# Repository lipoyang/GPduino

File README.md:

GPduino
=========

## 概要
GPduinoは、Arduino+Konashi互換のBLEラジコン制御ボードです。  
GPduinoに関する詳細は、[GPduino特設ページ](http://lipoyang.net/gpduino)をごらんください。  
GPduinoの回路/基板設計データとプリセットファームウェアのソースをここに公開します。

## ファイル一覧

* firm/GPduinoR3/ : ファームウェア(Arduino Pro Mini 3.3V 互換のスケッチ)
* hard/GPduinoPCB/
	* GPduino.sch/brd: 回路/基板設計データ(Eagle形式)
	* GPduino.pdf: 回路図(PDF)
	* GPduino_BOM.xlsx: BOMリスト(Excel形式)
	* GPduino.GBL/GBO/GBP/GBS/GML/GTL/GTO/GTP/GTS/TXT: ガーバデータ
* LICENSE: Apache Licence 2.0です。
	* ただし、回路/基板設計は、Creative Commons Attribution Share-Alike 3.0です。
* README.md これ

## ブートローダの書き込み
部品実装したGPduino基板をArduinoとして使用できるようにするには、まずブートローダを書き込みます。
* ISPコネクタ（CN12）にISPプログラマーを接続します。向きに注意してください。
	* 3.3V系のArduino (Arduino Pro Mini 3.3V版など)をISPプログラマーにすることができます。
	* File > Examples > Arduino ISP をArduinoに書き込んでください。
* Arduino IDEにて、Tools > Board で、Arduino Pro or Pro Mini を選びます。
* Tools > Processor で、ATmega328(3.3V, 8MHz) を選びます。
* Tools > Programmer で、ISPプログラマーを選びます。
	* 上記の、Arduinoを使ったISPプログラマーの場合は、Arduino as ISPを選んでください。
* Tools > Burn Bootloader で、ブートローダーを書き込みます。

## ファームウェアの書き込み
GPduinoは、Arduino Pro Mini 3.3V版互換機です。
* 書き込みはArduino Pro Miniと同様、USBシリアル変換基板が必要です。CN13に接続してください。
	* SparkFun製 FTDI Basic Breakout - 3.3V を推奨します。かならず、3.3Vのものを使用してください。
* 基板のジャンパJ3を[USB]側に設定してください。
* Arduino IDEにて、Tools > Board で、Arduino Pro or Pro Mini を選びます。
* Tools > Processor で、ATmega328(3.3V, 8MHz) を選びます。
* Tools > Port で、USBシリアルのポート番号を選びます。
* Uploadボタンで、ファームウェアを書き込みます。

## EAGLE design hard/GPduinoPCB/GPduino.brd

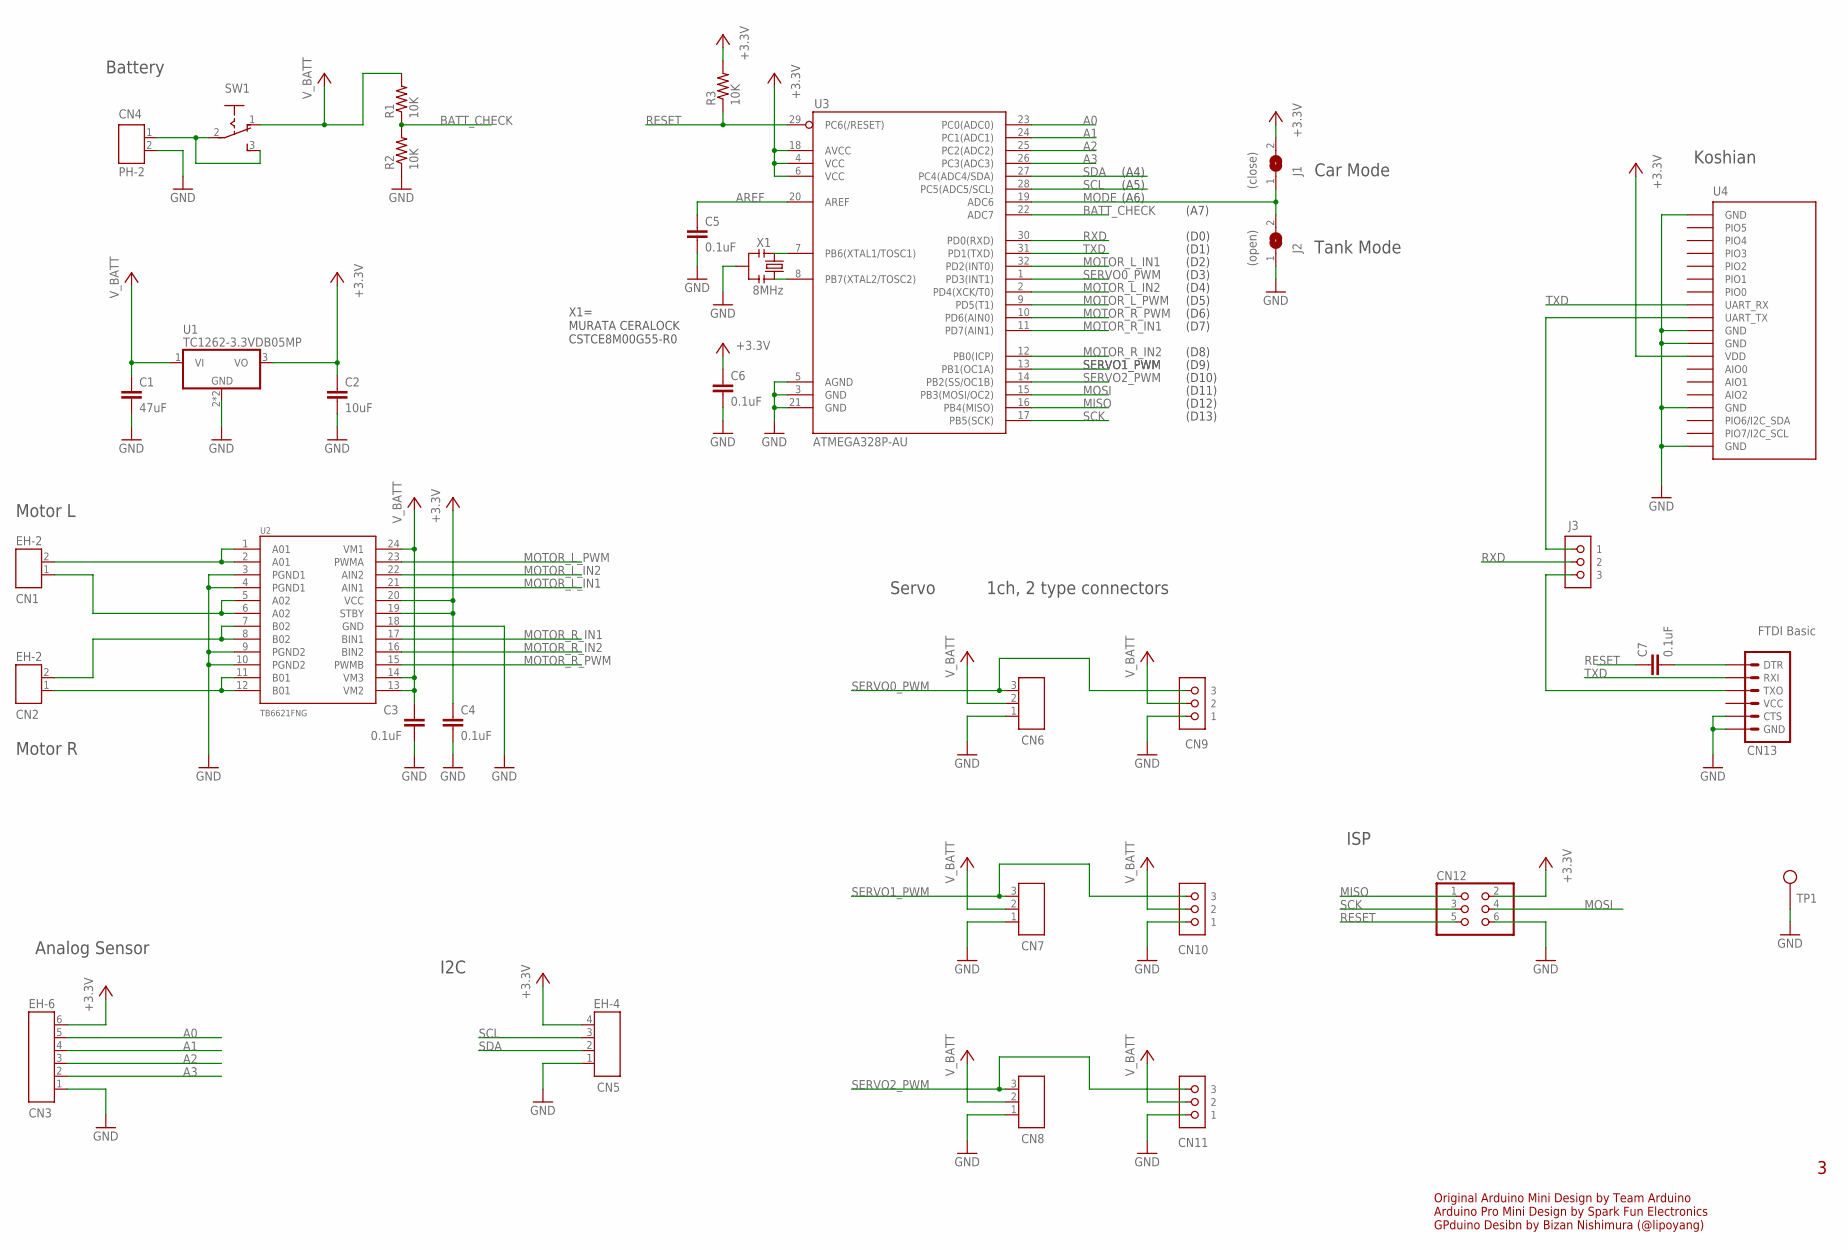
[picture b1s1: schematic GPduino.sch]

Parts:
C1: 47uF; C3216
C2: 10uF; C3216
C3, C4, C5, C6, C7: 0.1uF; C1608
CN1, CN2: EH-2
CN3: EH-6
CN4: PH-2
CN5: EH-4
CN6, CN7, CN8: PICOBLADE-3
CN9, CN10, CN11: cn6; CON_RC_SERVO
CN12: CN9; 2X03
CN13: FTDI Basic; 1X06
J1: (close); SJ
J2: (open); SJ
J3: XX-2; JUMPER_PIN_1X3
R1, R2, R3: 10K; 0603-RES
SW1: SW1; SLIDE-SW
TP1: TEST_PIN
U1: TC1262-3.3VDB05MP; SOT223
U2: TB6621FNG; SSOP24
U3: ATMEGA328P-AU; TQFP32-08
U4: KOSHIAN
X1: 8MHz; RESONATOR-SMD-1:1

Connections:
+3V3: C2.1, C4.1, C6.1, CN3.6, CN5.4, CN12.2, J1.2, R3.2, U1.3 (VO), U2.19 (STBY), U2.20 (VCC), U3.4 (VCC), U3.6 (VCC), U3.18 (AVCC), U4.12 (VDD)
A0: CN3.5, U3.23 (PC0(ADC0))
A01: CN1.2, U2.1 (A01), U2.2 (A01)
A1: CN3.4, U3.24 (PC1(ADC1))
A02: CN1.1, U2.5 (A02), U2.6 (A02)
A2: CN3.3, U3.25 (PC2(ADC2))
A3: CN3.2, U3.26 (PC3(ADC3))
AREF: C5.1, U3.20 (AREF)
BATT_CHECK: R1.1, R2.2, U3.22 (ADC7)
GND: C1.2, C2.2, C3.2, C4.2, C5.2, C6.2, CN3.1, CN4.2, CN5.1, CN6.1, CN7.1, CN8.1, CN9.1, CN10.1, CN11.1, CN12.6, CN13.5 (CTS), CN13.6 (GND), J2.1, R2.1, TP1.1, U1.2 (GND), U1.4 (GND), U2.3 (PGND1), U2.4 (PGND1), U2.9 (PGND2), U2.10 (PGND2), U2.18 (GND), U3.3 (GND), U3.5 (AGND), U3.21 (GND), U4.1 (GND), U4.10 (GND), U4.11 (GND), U4.16 (GND), U4.16@2 (GND), U4.20 (GND), X1.2
MISO: CN12.1, U3.16 (PB4(MISO))
MODE: J1.1, J2.2, U3.19 (ADC6)
MOSI: CN12.4, U3.15 (PB3(MOSI/OC2))
MOTOR_L_IN1: U2.21 (AIN1), U3.32 (PD2(INT0))
MOTOR_L_IN2: U2.22 (AIN2), U3.2 (PD4(XCK/T0))
MOTOR_L_PWM: U2.23 (PWMA), U3.9 (PD5(T1))
MOTOR_R_IN1: U2.17 (BIN1), U3.11 (PD7(AIN1))
MOTOR_R_IN2: U2.16 (BIN2), U3.12 (PB0(ICP))
MOTOR_R_PWM: U2.15 (PWMB), U3.10 (PD6(AIN0))
unnamed: CN4.1, SW1.2, SW1.3 (S)
unnamed: U3.8 (PB7(XTAL2/TOSC2)), X1.3
unnamed: U3.7 (PB6(XTAL1/TOSC1)), X1.1
unnamed: CN2.1, U2.11 (B01), U2.12 (B01)
unnamed: CN2.2, U2.7 (B02), U2.8 (B02)
unnamed: J3.1, U4.9 (UART_TX)
unnamed: C7.2, CN13.1 (DTR)
unnamed: CN13.3 (TXO), J3.3
RESET: C7.1, CN12.5, R3.1, U3.29 (PC6(/RESET))
RXD: J3.2, U3.30 (PD0(RXD))
SCK: CN12.3, U3.17 (PB5(SCK))
SCL: CN5.3, U3.28 (PC5(ADC5/SCL))
SDA: CN5.2, U3.27 (PC4(ADC4/SDA))
SERVO0_PWM: CN6.3, CN9.3, U3.1 (PD3(INT1))
SERVO1_PWM: CN7.3, CN10.3, U3.13 (PB1(OC1A))
SERVO2_PWM: CN8.3, CN11.3, U3.14 (PB2(SS/OC1B))
TXD: CN13.2 (RXI), U3.31 (PD1(TXD)), U4.8 (UART_RX), U4.8@2 (UART_RX)
V_BATT: C1.1, C3.1, CN6.2, CN7.2, CN8.2, CN9.2, CN10.2, CN11.2, R1.2, SW1.1 (O), U1.1 (VI), U2.13 (VM2), U2.14 (VM3), U2.24 (VM1)

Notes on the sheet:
Battery
Servo
Motor L
Original Arduino Mini Design by Team Arduino Arduino Pro Mini Design by Spark Fun Electronics GPduino Desibn by Bizan Nishimura (@lipoyang)
1ch, 2 type connectors
Analog Sensor
Motor R
ISP
Koshian
X1= MURATA CERALOCK CSTCE8M00G55-R0
Car Mode
Tank Mode
(D0)
(D1)
(D2)
(D3)
(D4)
(D5)
(D6)
(D7)
(D8)
(D9)
(D10)
(D11)
(D12)
(D13)
(A7)
(A6)
(A5)
(A4)
I2C

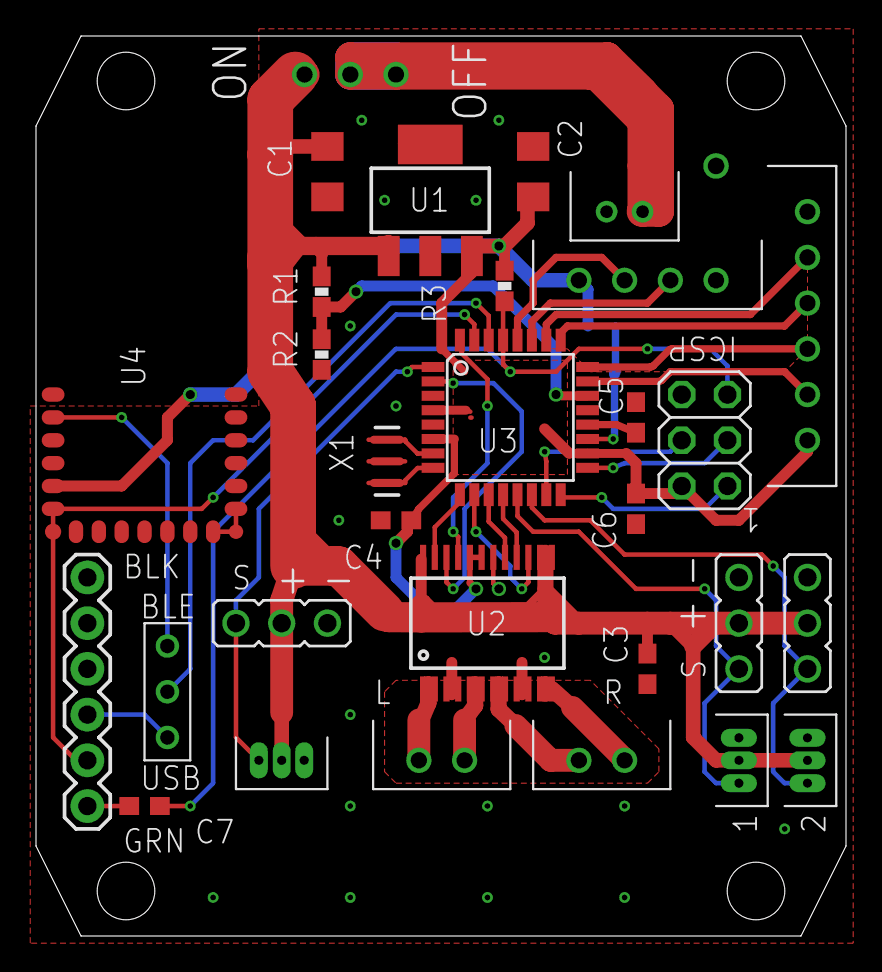
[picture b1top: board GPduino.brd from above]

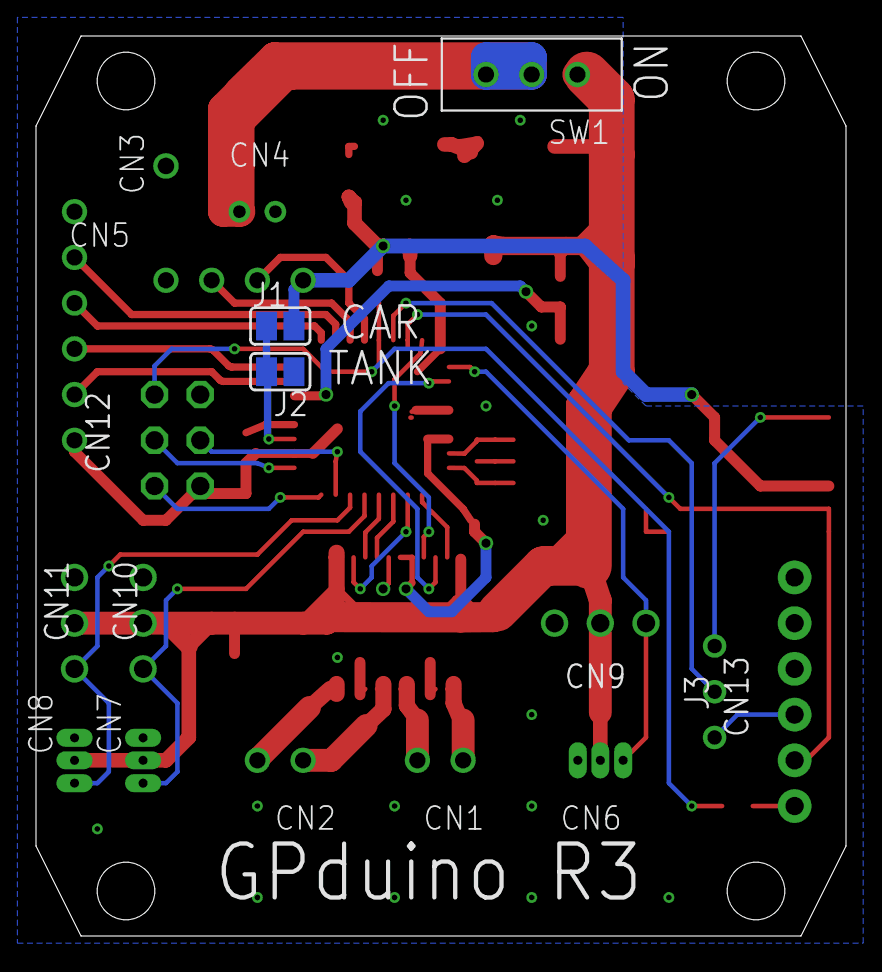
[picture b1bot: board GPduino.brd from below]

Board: 2 copper layers, 45.0 x 50.0 mm, 33 parts (3 on the bottom side), 37 nets.

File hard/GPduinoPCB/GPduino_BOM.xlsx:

GPduino BOM
基板本体キバンホンタイ
No | Reference | Part Number | Vender | Description | DNP | Qty | Unit Price | Price | Lot Size | Supplier | Supplier Code
1 | C1 | 47u(3216) | (generic) | 3216型ガタ |  | 1 | 30 | 30 | 10 | 秋月アキヅキ | P-06040
2 | C2 | 10u(3216) | (generic) | 3216型ガタ |  | 1 | 12.5 | 12.5 | 10 | 秋月アキヅキ | P-06462
3 | C3,4,5,6,7 | 0.1u(1608) | (generic) | 1608型ガタ |  | 4 | 0.32500000000000001 | 1.3 | 4000 | 秋月アキヅキ | P-01299
4 | CN1,2 | S2B-EH | JST | EH 2極 L型ポストキョクガタ | DNP | 0 | 16 | 0 | 1 | 共立キョウリツ | -
5 | CN3 | B6B-EH-A | JST | EH 6極 I型ポストキョクガタ | DNP | 0 | 27 | 0 | 1 | 共立キョウリツ | -
6 | CN4 | S2B-PH-K-S | JST | PH 2極 L型ポストキョクガタ |  | 1 | 16 | 16 | 1 | 共立キョウリツ | -
7 | CN5 | B4B-EH-A | JST | EH 4極 I型ポストキョクガタ | DNP | 0 | 21 | 0 | 1 | 共立キョウリツ | -
8 | CN6 | 53048-0310 | Molex | PicoBlade 3極 L型ポストキョクガタ | DNP (部品は付属)ブヒンフゾク | 1 | 45 | 45 | 5 | RS | 319-1092
9 | CN7,8 | 53047-0310 | Molex | PicoBlade 3極 I型ポストガタ | DNP | 0 | 29 | 0 | 5 | RS | 319-1064
10 | CN9 | - | (generic) | ピンヘッダ 3ピン | DNP (部品は付属)ブヒンフゾク | 1 | 35 | 35 | 16 | 共立キョウリツ | -
11 | CN10,11 | - | (generic) | ピンヘッダ 3ピン | DNP | 0 | 17 | 0 | 12 | 共立キョウリツ | -
12 | CN12 | - | (generic) | ピンヘッダ 2×3ピン I型ガタ | DNP | 0 | 70 | 0 | 1 | 共立キョウリツ | -
13 | CN13 | 0 | (generic) | ピンヘッダ 6ピン I型ガタ | DNP (部品は付属)ブヒンフゾク | 1 | 70 | 70 | 8 | 共立キョウリツ | -
14 | J3,SW1 | SS-12SDP2 | NKK | スライドスイッチ | DNP (部品は付属)ブヒンフゾク | 2 | 66 | 132 | 1 | 共立キョウリツ | 391139
15 | R1,2,3 | 10k(1608) | (generic) | 1608型 |  | 3 | 0.2 | 0.60000000000000009 | 2500 | 秋月アキヅキ | R-06103
16 | U1 | TC1262-3.3VDB05MP | Microchip | LDO, 3.3V-0.5A, SOT-223型ガタ |  | 1 | 81 | 81 | 1 | RS | 703-7905
17 | U2 | TB6621FNG | Toshiba | Dual DCモータドライバ |  | 1 | 306 | 306 | 1 | RS | 770-3797
18 | U3 | ATmega328P-AU | Atmel | AVRマイコン |  | 1 | 367 | 367 | 1 | RS | 696-3092
19 | U4 | Koshian | Macnica | BLEモジュール |  | 1 | 980 | 980 | 1 | Macnica | -
20 | X1 | CSTCE8M00G55-R0 | Murata | セラロック 8MHz |  | 1 | 45 | 45 | 10 | RS | 721-4821
21 | - | - | FusionPCB | 基板キバン |  | 1 | 241.7 | 241.7 | 10 | FusionPCB | -
22 | - | PH2P300L | Marutsu | PH 2極 アッセンブルケーブルキョク |  | 1 | 54 | 54 | 1 | マルツ | -
 |  |  |  |  |  |  | Total | 2417.1

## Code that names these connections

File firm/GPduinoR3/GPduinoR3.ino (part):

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#include "MovingAverage.h"

// ピン番号 (デジタル)
#define MOTOR_L_IN1    2
#define SERVO0_PWM     3
#define MOTOR_L_IN2    4
#define MOTOR_L_PWM    5
#define MOTOR_R_PWM    6
#define MOTOR_R_IN1    7
#define MOTOR_R_IN2    8
#define SERVO1_PWM     9
#define SERVO2_PWM     10

// ピン番号 (アナログ)
#define ANALOG_0      0
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#define ANALOG_2      2
#define ANALOG_3      3
#define MODE_CHECK    6
#define BATT_CHECK    7

// サーボ
Servo servo[3];
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    digitalWrite(MOTOR_L_IN2, LOW);
    digitalWrite(MOTOR_R_IN1, LOW);
    digitalWrite(MOTOR_R_IN2, LOW);
    pinMode(MOTOR_L_IN1, OUTPUT);
    pinMode(MOTOR_L_IN2, OUTPUT);
    pinMode(MOTOR_R_IN1, OUTPUT);
    pinMode(MOTOR_R_IN2, OUTPUT);
    
    // モード判定
    int mode_check = analogRead( MODE_CHECK );
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 */
void ctrl_motor(int ch, int val)
{
    static const int IN1[]={MOTOR_L_IN1, MOTOR_R_IN1};
    static const int IN2[]={MOTOR_L_IN2, MOTOR_R_IN2};
    static const int PWM[]={MOTOR_L_PWM, MOTOR_R_PWM};
    
    int l,r;
    int lpwm,rpwm,lin1,lin2,rin1,rin2;
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
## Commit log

2016-06-28 ファイル追加
2016-06-29 READMEの追記

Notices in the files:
parts and their libraries:
lipoyang_frame: Released under the Creative Commons
Attribution Share-Alike 3.0 License
http://creativecommons.org/licenses/by-sa/3.0
